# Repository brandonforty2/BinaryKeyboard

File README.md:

# BinaryKeyboard

A Keyboard that uses ASCII codes as inputs and outputs the corresponding letter.  There is also a mode where the keys work as 1, 0, and delete to make typing machine code easier for hardcore programmers.

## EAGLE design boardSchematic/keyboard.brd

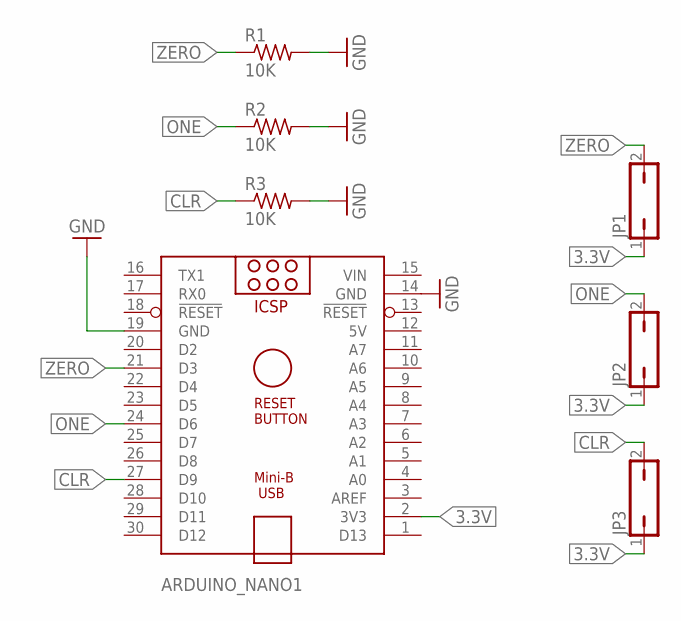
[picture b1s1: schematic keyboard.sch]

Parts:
ARDUINO_NANO1: ARDUINO_NANO
JP1, JP2, JP3: JP1Q; JP1
R1, R2, R3: 10K; 0207/12

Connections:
3.3V: ARDUINO_NANO1.2 (3V3), JP1.1, JP2.1, JP3.1
5V: ARDUINO_NANO1.12 (5V)
CLR: ARDUINO_NANO1.27 (D9), JP3.2, R3.1
GND: ARDUINO_NANO1.14 (GND), ARDUINO_NANO1.19 (GND), R1.2, R2.2, R3.2
ONE: ARDUINO_NANO1.24 (D6), JP2.2, R2.1
VIN: ARDUINO_NANO1.15 (VIN)
ZERO: ARDUINO_NANO1.21 (D3), JP1.2, R1.1

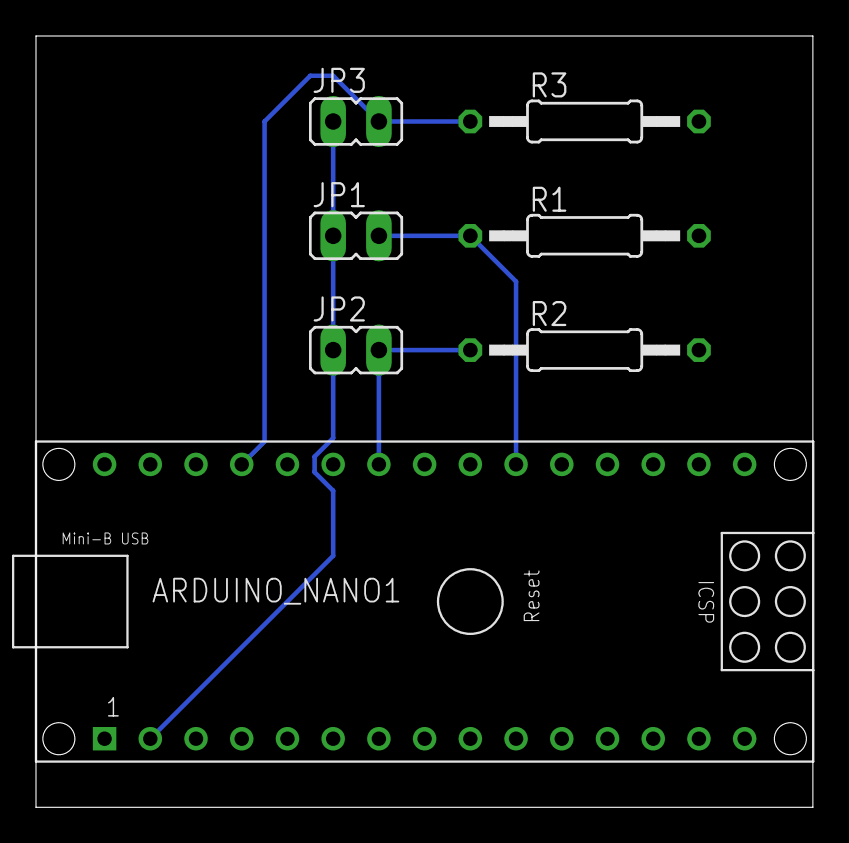
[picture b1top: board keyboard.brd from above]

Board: 2 copper layers, 43.2 x 42.9 mm, 7 parts (0 on the bottom side), 5 nets.

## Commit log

2019-01-16 Added PDF of board
2019-09-12 fixed typo
